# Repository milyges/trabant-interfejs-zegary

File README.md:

# trabant-interfejs-zegary
Konwerter sygnałów z silnika Swift na zegary VW Lupo - całość zamontowana jest w Trabancie

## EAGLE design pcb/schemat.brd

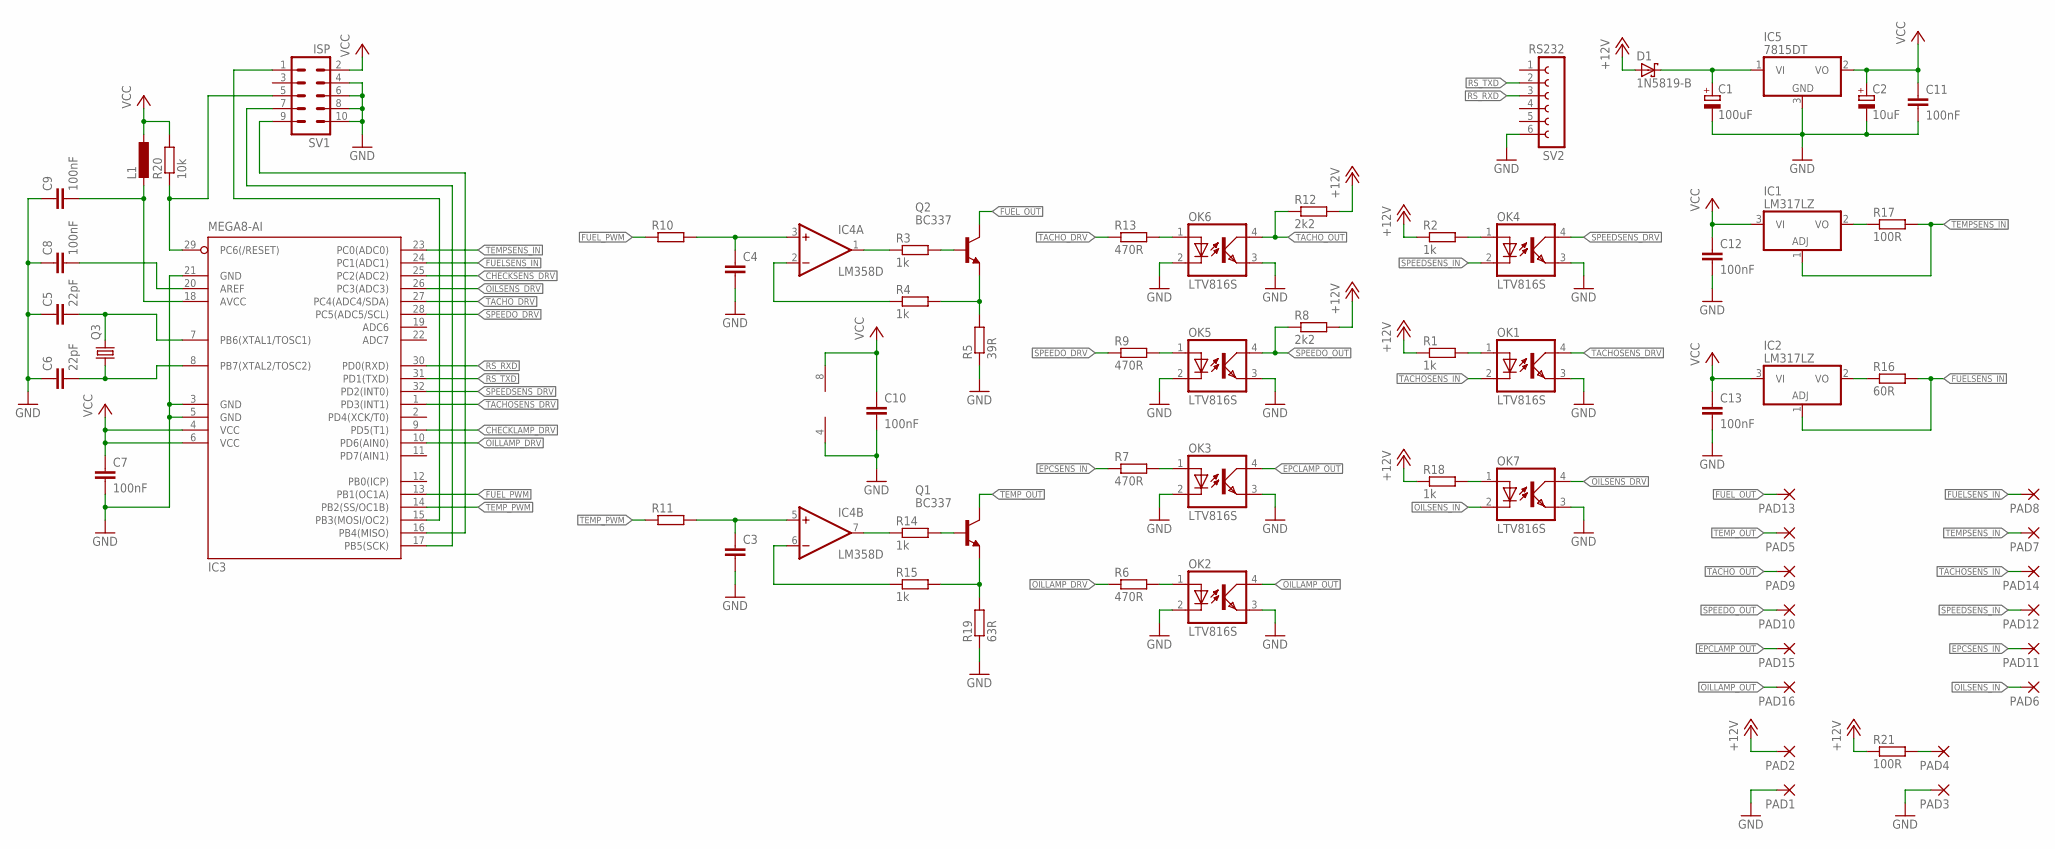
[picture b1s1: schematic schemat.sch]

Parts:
C1: 100uF; E2,5-6
C2: 10uF; E2,5-6
C3, C4: C-EU025-025X050; C025-025X050
C5, C6: 22pF; C0805
C7, C8, C9, C10, C11, C12, C13: 100nF; C0805
D1: 1N5819-B; DO41-7.6
IC1, IC2: LM317LZ; TO92
IC3: MEGA8-AI; TQFP32-08
IC4: LM358D; SO08
IC5: 7815DT; TO252
L1: L-EU0207/7; 0207/7
OK1, OK2, OK3, OK4, OK5, OK6, OK7: LTV816S; SMD4
PAD1, PAD2, PAD3, PAD4, PAD5, PAD6, PAD7, PAD8, PAD9, PAD10, PAD11, PAD12, PAD13, PAD14, PAD15, PAD16: 2,54/1,1
Q1, Q2: BC337; TO92
Q3: CRYSTALHC49UP; HC49UP
R1, R2, R3, R4, R14, R15, R18: 1k; M0805
R5: 39R; M0805
R6, R7, R9, R13: 470R; M0805
R8, R12: 2k2; M0805
R10, R11: R-EU_M0805; M0805
R16: 60R; M0805
R17, R21: 100R; M0805
R19: 63R; M0805
R20: 10k; M0805
SV1: ISP; ML10L
SV2: RS232; FE06

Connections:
+12V: D1.A, PAD2.1, R1.1, R2.1, R8.2, R12.2, R18.1, R21.1
CHECKLAMP_DRV: IC3.9 (PD5(T1))
CHECKSENS_DRV: IC3.25 (PC2(ADC2))
EPCLAMP_OUT: OK3.4 (COL), PAD15.1
EPCSENS_IN: PAD11.1, R7.1
FUELSENS_IN: IC2.1 (ADJ), IC3.24 (PC1(ADC1)), PAD8.1, R16.2
FUEL_OUT: PAD13.1, Q2.3 (C)
FUEL_PWM: IC3.13 (PB1(OC1A)), R10.1
GND: C1.-, C2.-, C3.2, C4.2, C5.1, C6.1, C7.2, C8.1, C9.1, C10.2, C11.2, C12.2, C13.2, IC3.3 (GND), IC3.5 (GND), IC3.21 (GND), IC4.4 (V-), IC5.3 (GND), OK1.3 (EMIT), OK2.2 (C), OK2.3 (EMIT), OK3.2 (C), OK3.3 (EMIT), OK4.3 (EMIT), OK5.2 (C), OK5.3 (EMIT), OK6.2 (C), OK6.3 (EMIT), OK7.3 (EMIT), PAD1.1, PAD3.1, R5.1, R19.1, SV1.4, SV1.6, SV1.8, SV1.10, SV2.6
unnamed: PAD4.1, R21.2
unnamed: Q2.2 (B), R3.2
unnamed: IC4.1 (OUT), R3.1
unnamed: Q2.1 (E), R4.2, R5.2
unnamed: IC4.2 (-IN), R4.1
unnamed: C4.1, IC4.3 (+IN), R10.2
unnamed: Q1.2 (B), R14.2
unnamed: IC4.7 (OUT), R14.1
unnamed: Q1.1 (E), R15.2, R19.2
unnamed: IC4.6 (-IN), R15.1
unnamed: C3.1, IC4.5 (+IN), R11.2
unnamed: OK2.1 (A), R6.2
unnamed: OK6.1 (A), R13.2
unnamed: OK5.1 (A), R9.2
unnamed: OK3.1 (A), R7.2
unnamed: OK1.1 (A), R1.2
unnamed: OK7.1 (A), R18.2
unnamed: IC1.2 (VO), R17.1
unnamed: OK4.1 (A), R2.2
unnamed: C1.+, D1.C, IC5.1 (VI)
unnamed: IC2.2 (VO), R16.1
unnamed: C6.2, IC3.8 (PB7(XTAL2/TOSC2)), Q3.1
unnamed: C5.2, IC3.7 (PB6(XTAL1/TOSC1)), Q3.2
unnamed: C8.2, IC3.20 (AREF)
unnamed: C9.2, IC3.18 (AVCC), L1.2
unnamed: IC3.29 (PC6(/RESET)), R20.1, SV1.5
unnamed: IC3.15 (PB3(MOSI/OC2)), SV1.1
unnamed: IC3.17 (PB5(SCK)), SV1.7
unnamed: IC3.16 (PB4(MISO)), SV1.9
OILLAMP_DRV: IC3.10 (PD6(AIN0)), R6.1
OILLAMP_OUT: OK2.4 (COL), PAD16.1
OILSENS_DRV: IC3.26 (PC3(ADC3)), OK7.4 (COL)
OILSENS_IN: OK7.2 (C), PAD6.1
RS_RXD: IC3.30 (PD0(RXD)), SV2.3
RS_TXD: IC3.31 (PD1(TXD)), SV2.2
SPEEDO_DRV: IC3.28 (PC5(ADC5/SCL)), R9.1
SPEEDO_OUT: OK5.4 (COL), PAD10.1, R8.1
SPEEDSENS_DRV: IC3.32 (PD2(INT0)), OK4.4 (COL)
SPEEDSENS_IN: OK4.2 (C), PAD12.1
TACHOSENS_DRV: IC3.1 (PD3(INT1)), OK1.4 (COL)
TACHOSENS_IN: OK1.2 (C), PAD14.1
TACHO_DRV: IC3.27 (PC4(ADC4/SDA)), R13.1
TACHO_OUT: OK6.4 (COL), PAD9.1, R12.1
TEMPSENS_IN: IC1.1 (ADJ), IC3.23 (PC0(ADC0)), PAD7.1, R17.2
TEMP_OUT: PAD5.1, Q1.3 (C)
TEMP_PWM: IC3.14 (PB2(SS/OC1B)), R11.1
VCC: C2.+, C7.1, C10.1, C11.1, C12.1, C13.1, IC1.3 (VI), IC2.3 (VI), IC3.4 (VCC), IC3.6 (VCC), IC4.8 (V+), IC5.2 (VO), L1.1, R20.2, SV1.2

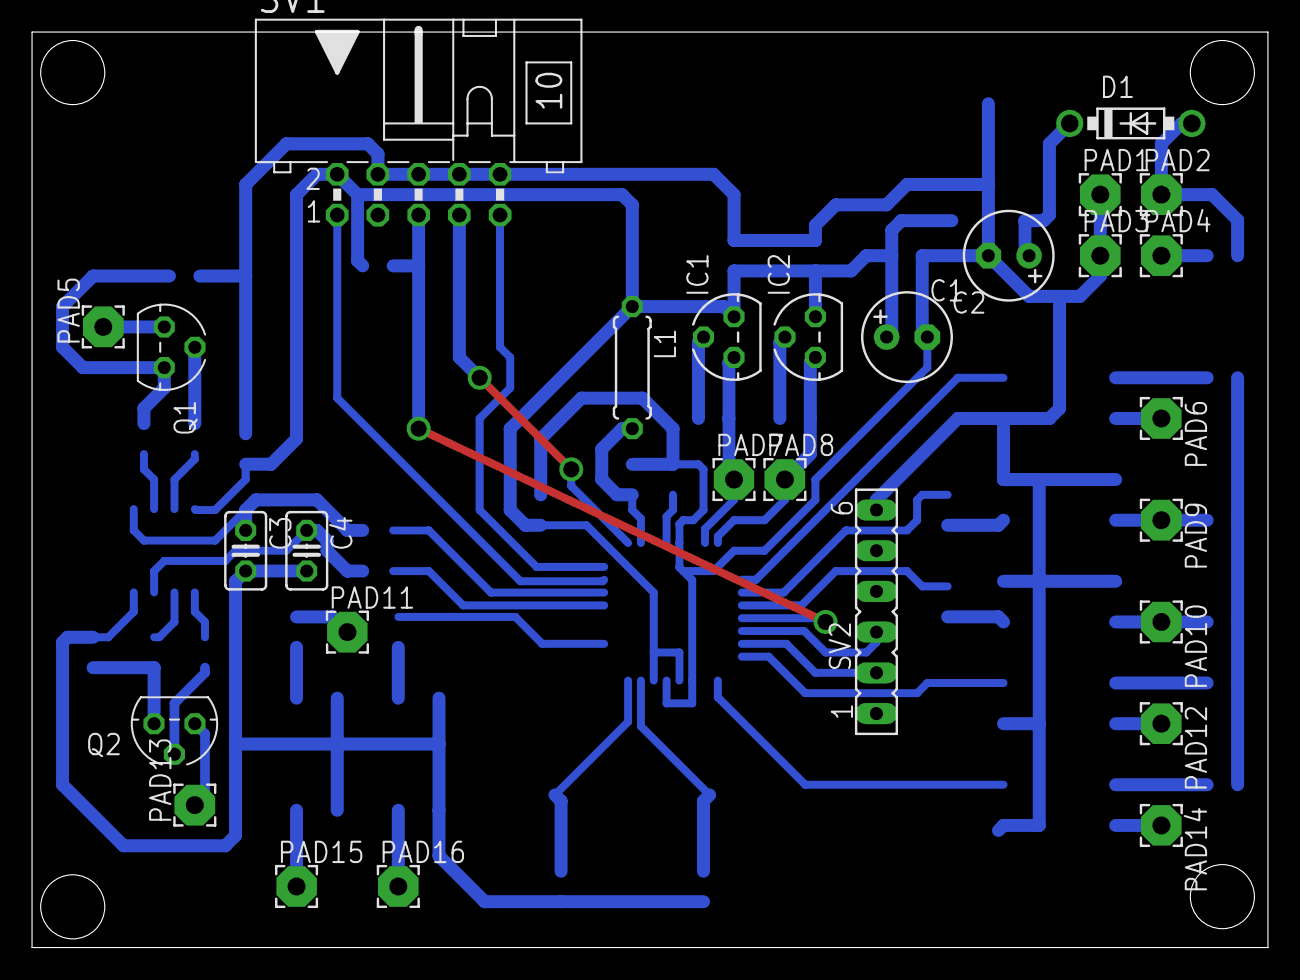
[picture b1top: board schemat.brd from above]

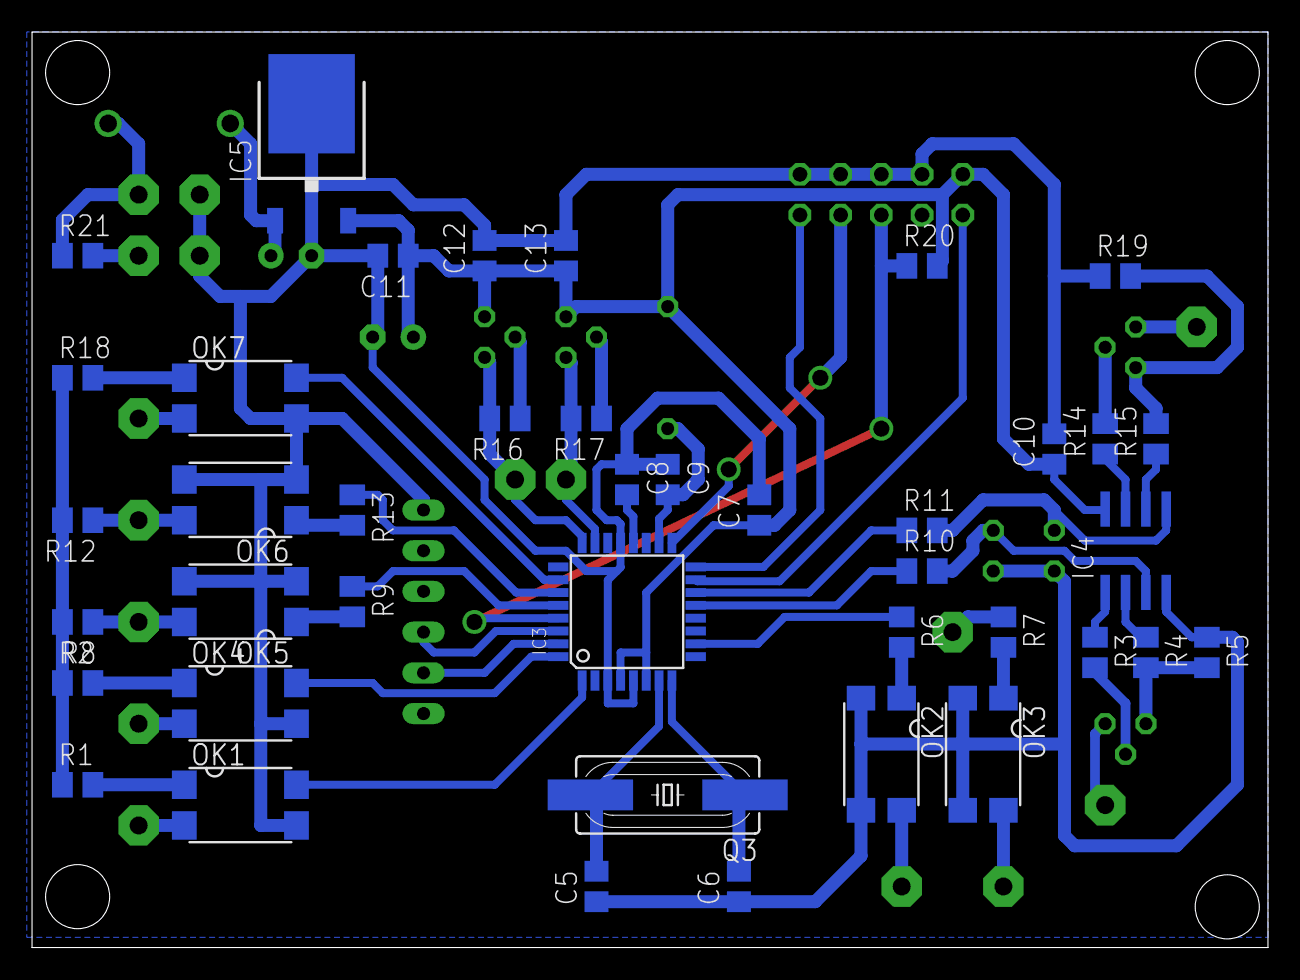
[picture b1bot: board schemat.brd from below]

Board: 2 copper layers, 77.1 x 57.1 mm, 69 parts (41 on the bottom side), 54 nets.

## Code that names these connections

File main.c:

#include <avr/io.h>
#include <avr/interrupt.h>
#include <util/delay.h>
#include <stdio.h>

#define TACHOOUT_DDR     DDRC
#define TACHOOUT_PORT    PORTC
#define TACHOOUT_PINNO   PC4

#define SPEEDOUT_DDR     DDRC
#define SPEEDOUT_PORT    PORTC
#define SPEEDOUT_PINNO   PC5

#define TEMPOUT_DDR      DDRB
#define TEMPOUT_PINNO    PB2
#define TEMPOUT_OCR      OCR1B

#define FUELOUT_DDR      DDRB
#define FUELOUT_PINNO    PB1
#define FUELOUT_OCR      OCR1A

#define OILOUT_DDR       DDRD
#define OILOUT_PORT      PORTD
#define OILOUT_PINNO     PD6

#define SPEEDIN_DDR      DDRD
#define SPEEDIN_PORT     PORTD
#define SPEEDIN_PINNO    PD2

#define TACHOIN_DDR      DDRD
#define TACHOIN_PORT     PORTD
#define TACHOIN_PINNO    PD3

#define FUELIN_DDR       DDRC
#define FUELIN_PINNO     PC1
#define FUELIN_ADC       1

#define TEMPIN_DDR       DDRC
#define TEMPIN_PINNO     PC0
#define TEMPIN_ADC       0

#define OILIN_DDR        DDRC
#define OILIN_PORT       PORTC
#define OILIN_PIN        PINC
#define OILIN_PINNO      PC3

#define OILIN_READ()     ((OILIN_PIN & (1 << OILIN_PINNO)) == (1 << OILIN_PINNO))
#define OILOUT_WRITE(x)  OILOUT_PORT = (x) ? (OILOUT_PORT | (1 << OILOUT_PINNO)) : (OILOUT_PORT & ~(1 << OILOUT_PINNO))

#define USART_BAUDRATE  9600
#define USART_UBR       (F_CPU / 16 / USART_BAUDRATE - 1)

static uint16_t _rpm_val = 0xFFFF;
static uint16_t _speed_val = 0xFFFF;
static volatile uint16_t _int0_imp;
static volatile uint16_t _int1_imp;
static volatile uint16_t _rpm_input;
static volatile uint8_t _speed_input;
static volatile uint8_t _temp_input;
static volatile uint8_t _fuel_input;

/* Przerwanie Timer0 - generowanie przebiegów dla prędkościomierza i obrotomierza */
ISR(TIMER0_OVF_vect) {
	static uint16_t rpm_cnt = 0;
	static uint16_t speed_cnt = 0;
	
	if (!rpm_cnt) {
		if (_rpm_val != 0xFFFF) {
			TACHOOUT_PORT ^= (1 << TACHOOUT_PINNO);
		}
		rpm_cnt = _rpm_val;
	}
		
	if (!speed_cnt) {
		if (_speed_val != 0xFFFF) {
			SPEEDOUT_PORT ^= (1 << SPEEDOUT_PINNO);
		}
		speed_cnt = _speed_val;
	}
	
	rpm_cnt--; speed_cnt--;
	
	TCNT0 = 248; // 256 - 2^3
}

/*
 * Dla 1000 -> 18
 * Dla 2000 -> 2*18
 * 
 * 
 * */
/* Timer 2 do zliczania impulsów w czasie, przepiełnia z f = 8MHz / 1024 / 256 = 30.52Hz */
ISR(TIMER2_OVF_vect) {
	static uint8_t int0_counter = 0;
        static uint8_t int1_counter = 0;
	uint32_t int0, int1;

	if (int1_counter >= 4) { /* To nadal za dużo - zmniejszamy aby przepełniał się co 30.5 / 4 = 6.1Hz */		
		int1 = _int1_imp; _int1_imp = 0;
		
                _rpm_input = int1 * 1000 / 18;
		int1_counter = 0;
	}
	else {
		int1_counter++;
	}
	
	if (int0_counter >= 4) {
		int0 = _int0_imp; _int0_imp = 0;
		
		_speed_input = int0;
		int0_counter = 0;
	}
	else {
		int0_counter++;
	}
}

/* Przerwanie od impulsów z prędkościomierza */
ISR(INT0_vect) {
	_int0_imp++;
}

/* Przerwanie od impulsów z obrotomierza */
ISR(INT1_vect) {
	_int1_imp++;	
}

ISR(ADC_vect) {
	uint8_t chan = ADMUX & 0x0F;
	uint8_t i, tmp;
	/* Temperatura / 10 => Wartość ADC począwszy od 40C */
	static uint8_t temp2adc[] = {
		254, /* 40C */
		204, /* 50C */
		130, /* 60C */
		89,  /* 70C */
		64,  /* 80C */
		48,  /* 90C */
		37,  /* 100C */
		29,  /* 110C */
		23,  /* 120C */
		19,  /* 130C */
		16,  /* 140C */
	};
	
	/* Sprawdzamy który kanal byl probkowany */
	if (chan == TEMPIN_ADC) {
		tmp = ADCH;
		for(i = 0; i < sizeof(temp2adc) / sizeof(uint8_t); i++) {
			if (temp2adc[i] <= tmp) {
				break;
			}
		}
		
		/* Błąd */
		if (i == 0) { /* Silnik bardzo zimny / błąd */
			_temp_input = 0;
		}
		if (i >= sizeof(temp2adc) / sizeof(uint8_t)) { /* Silnik bardzo gorący / błąd */
			_temp_input = 0xFF;
		}
		else {
			uint8_t a, b;
			a = tmp - temp2adc[i];
			b = temp2adc[i - 1] - tmp;
			_temp_input = 
			_temp_input = (((i * b) + ((i - 1) * a)) * 10) / (a + b) + 40;
		}
		
		chan = FUELIN_ADC;
	}
	else if (chan == FUELIN_ADC) {
		_fuel_input = ADCH;
		chan = TEMPIN_DDR;
	}
	else {
		/* Nigdy nie powinnismy tu trafic */
	}
	
	/* Rozpoczynamy kolejne probkowanie */
	ADMUX = (1 << REFS1) | (1 << REFS0) | (1 << ADLAR) | chan;
	ADCSRA |= (1 << ADSC);
}

static int printf_helper(char c, FILE * stream) {
	if (c == '\n') 	{
		_delay_ms(1);
		while(!(UCSRA & (1 << UDRE)));
		UDR = '\r';
	}
	_delay_ms(1);
	while(!(UCSRA & (1 << UDRE)));
	UDR = c;

	return 0;
}

static FILE _stdout = FDEV_SETUP_STREAM(printf_helper, NULL, _FDEV_SETUP_WRITE);

void adc_start(uint8_t chan) {
	
}

void init(void) {
	/* Debugowanie po USART */
	UBRRH = (unsigned char)(USART_UBR >> 8);
	UBRRL = (unsigned char)USART_UBR;
	UCSRB = (1 << TXEN) | (1 << RXEN);
	UCSRC = (1 << URSEL) | (3 << UCSZ0);
	stdout = &_stdout;
	
	/* Wyjścia prędkościomierza i obrotomierza */
	TACHOOUT_DDR |= (1 << TACHOOUT_PINNO);
	TACHOOUT_PORT &= ~(1 << TACHOOUT_PINNO);
	
	SPEEDOUT_DDR |= (1 << SPEEDOUT_PINNO);
	SPEEDOUT_PORT &= ~(1 << SPEEDOUT_PINNO);
	
	/* PWM dla temperatury i poziomu paliwa */
	TEMPOUT_DDR |= (1 << TEMPOUT_PINNO);
	FUELOUT_DDR |= (1 << FUELOUT_PINNO);	
	TCCR1A |= (1 << COM1A1) | (1 << COM1B1) | (1 << WGM11) | (1 << WGM10);
	TCCR1B |= (0 << CS12) | (1 << CS11) | (0 << CS10); 
	
	/* Lampka kontrolna oleju */
	OILOUT_DDR |= (1 << OILOUT_PINNO);
	
	/* Wejście czujnika ciśnienia oleju */
	OILIN_DDR &= ~(1 << OILIN_PINNO);
	OILIN_PORT |= (1 << OILIN_PINNO);
	
	/* Przerwania wejściowe dla impulsów prędkościomierza i obrotomierza */
	SPEEDIN_DDR &= ~(1 << SPEEDIN_PINNO);
	SPEEDIN_PORT |=  (1 << SPEEDIN_PINNO);
	TACHOIN_DDR &= ~(1 << TACHOIN_PINNO);
	TACHOIN_PORT |=  (1 << TACHOIN_PINNO);
	MCUCR |= (1 << ISC11) | (1 << ISC10) | (1 << ISC01) | (1 << ISC00); /* Aktywacja zboczem narastającym */
	GICR |= (1 << INT1) | (1 << INT0);
	GIFR |= (1 << INTF1) | (1 << INTF0); /* Asekuracyjnie zerujemy flagi przerwań */
	
	/* Wejście czujnika paliwa i temperatury */
	TEMPIN_DDR &= ~(1 << TEMPIN_PINNO);
	FUELIN_DDR &= ~(1 << FUELIN_PINNO);
	
	/* Inicjujemy ADC i rozpoczynamy pierwsza konwersje */
	ADMUX = (1 << REFS1) | (1 << REFS0) | (1 << ADLAR) | TEMPIN_ADC;
	ADCSRA = (1 << ADEN) | (1 << ADIF) | (1 << ADIE) | (1 << ADPS2) | (1 << ADPS1) | (1 << ADPS0);
		
	/* Timer 0 - generowanie przebiegów dla prędkościomierza i obrotomierza */
	TCCR0 |= (0 << CS02) | (1 << CS01) | (1 << CS00);
	TIMSK |= (1 << TOIE0);
	TIFR |= (1 << TOV0);
	
	/* Timer 2 - odm,ierzanie czasu  */
	TCCR2 |= (1 << CS22) | (1 << CS21) | (1 << CS20);
	TIMSK |= (1 << TOIE2);
	TIFR |= (1 << TOV2);
	
	sei(); /* Globalna aktywacja przerwań */
	
	ADCSRA |= (1 << ADSC); /* uruchamiamy pierwsza konwersje na ADC */
}

void setout_rpm(uint16_t rpm) {
	if (!rpm) {
		_rpm_val = 0xFFFF;
	}
	else {
		uint32_t a = (rpm / 250); 
		uint32_t b = (rpm % 250);
		_rpm_val = (uint32_t)(((960 / (a + 1)) * b) + ((960 / a) * (250 - b))) / 250;
	}
}

void setout_speed(uint8_t speed) {
	if (!speed) {
		_speed_val = 0xFFFF;
	}
	else {
		uint32_t a = speed / 5;
		uint32_t b = speed % 5;
		_speed_val = (((1452 / (a + 1) * b) + ((1452 / a) * (5 - b))) / 5);
	}
}

void setout_fuel(uint8_t level) {
	/* Poziom paliwa w % co 25% */
	static uint16_t fuel2val[] = {
		0x1A0, /* 0 */
		0x136, /* 25% */
		0xFE,  /* 50% */
		0xD6,  /* 75% */
		0xB0,  /* 100 */
		0xB0,  /* 100 */
	};

	if (level > 100)
		level = 100;
	
	uint32_t a = level / 25;
	uint32_t b = level % 25;
	FUELOUT_OCR = ((fuel2val[a + 1] * b) + (fuel2val[a] * (25 - b))) / 25;
}

void setout_temp(uint8_t temp) {
	/* Temperatura / 10 => wartość PWM. Minimalna wartość 50C */
	static uint16_t temp2val[] = {
		0x20, /* 50C */
		0x38, /* 60C */
		0x40, /* 70C */
		0x48, /* 80C */
		0x80, /* 90C */
		0x88, /* 100C */
		0x8E, /* 110C */
		0x96, /* 120C */
		0x9E, /* 130C */
		0x9E, /* 130C */
	};
	
	if (temp < 50) {
		temp = 50;
	}
	else if (temp > 130) {
		temp = 130;
	}
		
	temp -= 50;
	uint32_t a = temp / 10;
	uint32_t b = temp % 10;
	TEMPOUT_OCR = ((temp2val[a + 1] * b) + (temp2val[a] * (10 - b))) / 10;
}

int main(void) {
	init();
	
	setout_speed(0);
	setout_fuel(50);
	setout_temp(0);
	setout_rpm(0);
	uint16_t oldrpm = 0;
	uint8_t oldspeed = 0;
	
	
	while(1) {
		if (oldrpm != _rpm_input) {
			oldrpm = _rpm_input;
			setout_rpm(oldrpm);
		}
		
		if (oldspeed != _speed_input) {
			oldspeed = _speed_input;
			setout_speed(_speed_input);
		}
		
		/* Czujnik cisnienia oleju odczytujemy tylko jak silnik pracuje - wejście negujemy */
		if (_rpm_input > 1450) {
			OILOUT_WRITE(OILIN_READ());
			//OILOUT_WRITE(1);
		}
		else {
			OILOUT_WRITE(0);
		}
		
		if ((_temp_input == 0) || (_temp_input == 0xFF)) {
			setout_temp(0);
		}
		else {
			setout_temp(_temp_input);
		}
		printf("rpm=%u,speed=%u,temp=%u,fuel=%u,oil=%u\n", _rpm_input, _speed_input, _temp_input, _fuel_input, OILIN_READ());
	}
	return 0;
}

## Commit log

2016-11-16 Import kodu źródłowego
2016-11-16 Import projektu PCB i schematu
2016-11-16 Lierówki w .gitignore
